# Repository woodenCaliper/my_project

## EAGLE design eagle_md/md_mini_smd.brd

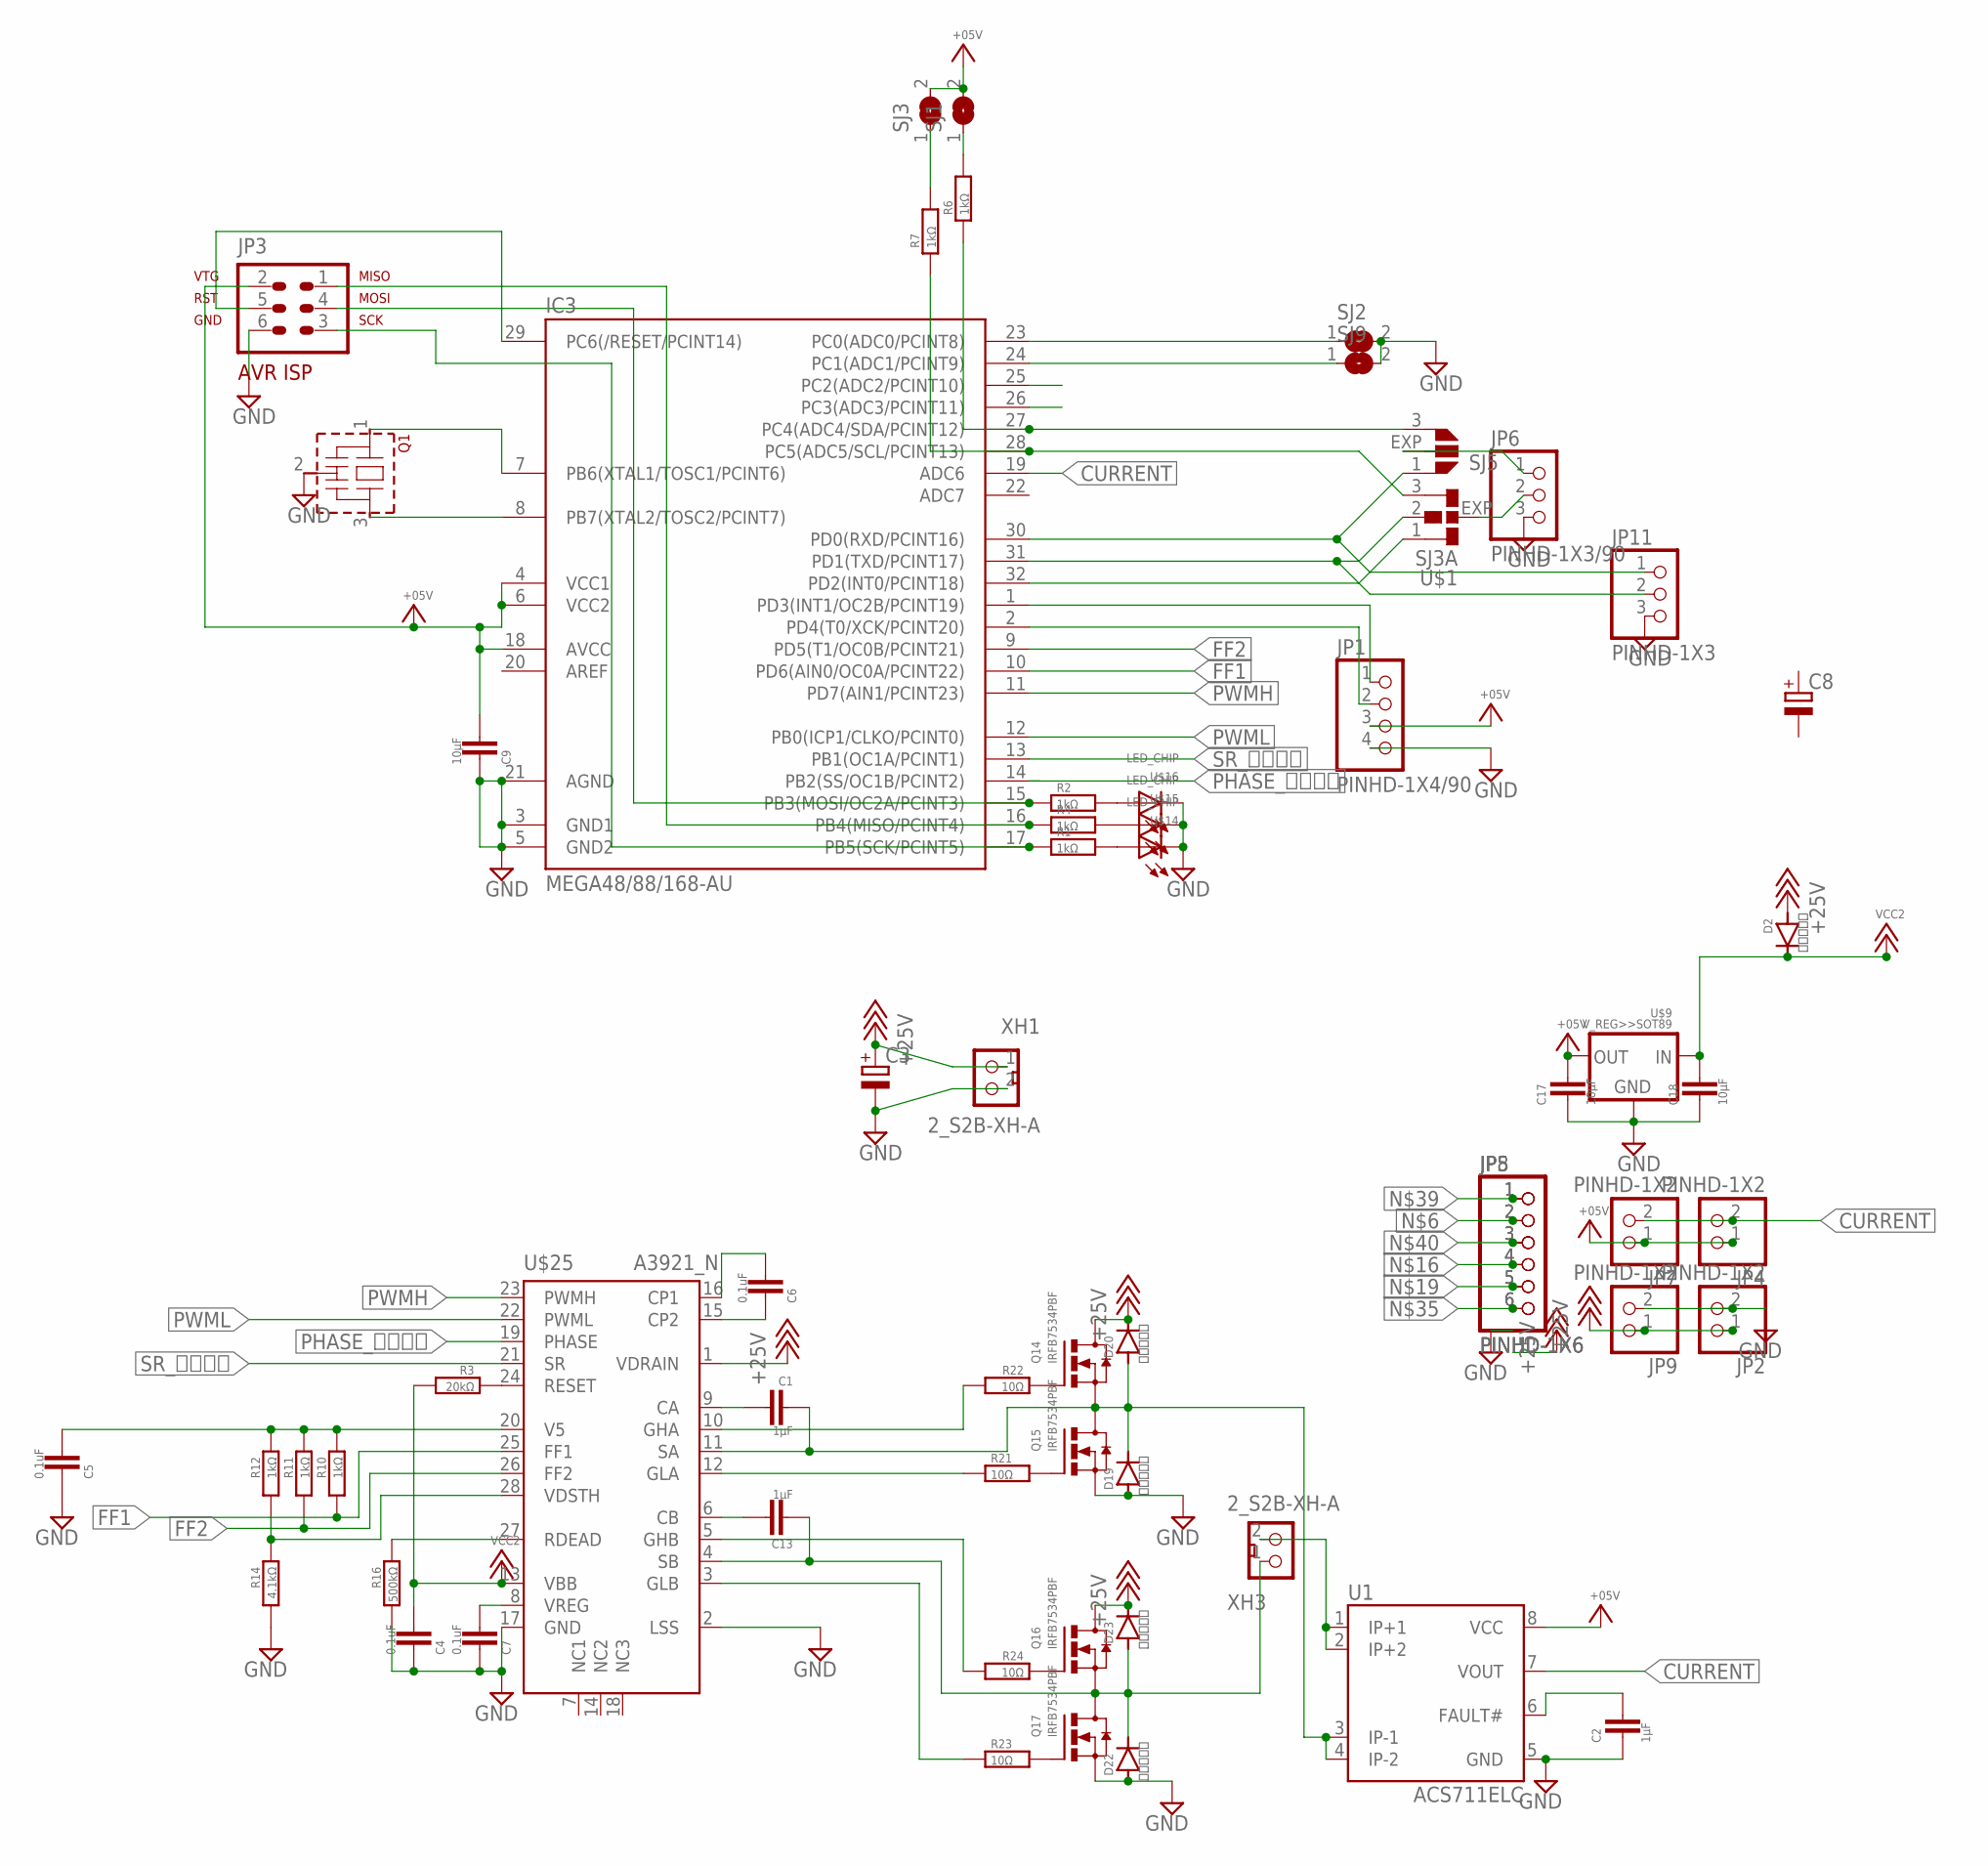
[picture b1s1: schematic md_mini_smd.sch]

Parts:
C1, C2, C13: 1μF; 2012
C3: CPOL-EUUD-6,3X8,8; UD-6,3X5,8_NICHICON
C4, C5, C6, C7: 0.1uF; 2012
C8: CPOL-EU150CLZ-1010; 150CLZ-1010
C9, C17, C18: 10μF; 2012
D2, D19, D20, D22, D23: ＭＳ１８Ｆ; MS18F
IC3: MEGA48/88/168-AU; TQFP32-08
JP1: PINHD-1X4/90; 1X04/90
JP2, JP4, JP7, JP9: PINHD-1X2; 1X02
JP3: AVR-ISP-6
JP5, JP8: PINHD-1X6; 1X06
JP6: PINHD-1X3/90; 1X03/90
JP11: PINHD-1X3; 1X03
Q1: CSTLS_G; CSTLS_G8
Q14, Q15, Q16, Q17: IRFB7534PBF; TO252
R1, R2, R4, R6, R7, R10, R11, R12: 1kΩ; 1608
R3: 20kΩ; 1608
R14: 4.1kΩ; 1608
R16: 500kΩ; 1608
R21, R22, R23, R24: 10Ω; 1608
SJ1, SJ2, SJ3, SJ9: SJSS; SJ_B
SJ5: SJ2; SJ2_A
U1: ACS711ELC; SOIC8
U$1: SJ3A; SJ3_A
U$9: V_REG>>SOT89; SOT89
U$14, U$15, U$16: LED_CHIP; 2012
U$25: A3921_N; TSSOP28_N
XH1, XH3: 2_S2B-XH-A; S2B-XH-A

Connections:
+5V: C9.1, C17.1, IC3.4 (VCC1), IC3.6 (VCC2), IC3.18 (AVCC), JP1.3, JP3.2, JP4.1, JP7.1, SJ1.2, SJ3.2, U1.8 (VCC), U$9.1 (OUT)
+18V: C3.+, D2.P$1 (A), D20.P$2 (C), D23.P$2 (C), JP2.1, JP9.1, Q14.3 (D), Q16.3 (D), U$25.1 (VDRAIN), XH1.1
CURRENT: IC3.19 (ADC6), JP4.2, JP7.2, U1.7 (VOUT)
FF1: IC3.10 (PD6(AIN0/OC0A/PCINT22)), R10.2, U$25.25 (FF1)
FF2: IC3.9 (PD5(T1/OC0B/PCINT21)), R11.2, U$25.26 (FF2)
GND: C2.2, C3.-, C4.2, C5.2, C7.2, C9.2, C17.2, C18.2, D19.P$1 (A), D22.P$1 (A), IC3.3 (GND1), IC3.5 (GND2), IC3.21 (AGND), JP1.4, JP2.2, JP3.6, JP6.3, JP9.2, JP11.3, Q1.2 (VSS), Q15.2 (S), Q17.2 (S), R14.2, R16.2, SJ2.2, SJ9.2, U1.5 (GND), U$9.2 (GND), U$9.2.1 (GND), U$14.P$2 (C), U$15.P$2 (C), U$16.P$2 (C), U$25.2 (LSS), U$25.17 (GND), XH1.2
unnamed: IC3.1 (PD3(INT1/OC2B/PCINT19)), JP1.1
unnamed: R6.2, SJ1.1
unnamed: U1.1 (IP+1), U1.2 (IP+2), XH3.2
unnamed: C6.1, U$25.16 (CP1)
unnamed: IC3.29 (PC6(/RESET/PCINT14)), JP3.5
unnamed: C13.2, D22.P$2 (C), D23.P$1 (A), JP5.2, JP8.2, Q16.2 (S), Q17.3 (D), U$25.4 (SB), XH3.1
unnamed: IC3.7 (PB6(XTAL1/TOSC1/PCINT6)), Q1.1
unnamed: IC3.8 (PB7(XTAL2/TOSC2/PCINT7)), Q1.3
unnamed: R1.2, U$14.P$1 (A)
unnamed: IC3.2 (PD4(T0/XCK/PCINT20)), JP1.2
unnamed: IC3.17 (PB5(SCK/PCINT5)), JP3.3, R1.1
unnamed: C1.1, U$25.9 (CA)
unnamed: R4.2, U$15.P$1 (A)
unnamed: JP5.4, JP8.4, R22.2, U$25.10 (GHA)
unnamed: R2.2, U$16.P$1 (A)
unnamed: JP6.2, U$1.EXP
unnamed: C1.2, D19.P$2 (C), D20.P$1 (A), JP5.5, JP8.5, Q14.2 (S), Q15.3 (D), U1.3 (IP-1), U1.4 (IP-2), U$25.11 (SA)
unnamed: R7.2, SJ3.1
unnamed: IC3.15 (PB3(MOSI/OC2A/PCINT3)), JP3.4, R2.1
unnamed: IC3.16 (PB4(MISO/PCINT4)), JP3.1, R4.1
unnamed: JP6.1, SJ5.EXP (2)
unnamed: IC3.32 (PD2(INT0/PCINT18)), U$1.1
unnamed: IC3.23 (PC0(ADC0/PCINT8)), SJ2.1
unnamed: IC3.24 (PC1(ADC1/PCINT9)), SJ9.1
unnamed: IC3.31 (PD1(TXD/PCINT17)), JP11.2, U$1.2
unnamed: IC3.30 (PD0(RXD/PCINT16)), JP11.1, SJ5.1
unnamed: C6.2, U$25.15 (CP2)
unnamed: IC3.28 (PC5(ADC5/SCL/PCINT13)), R7.1, U$1.3
unnamed: IC3.27 (PC4(ADC4/SDA/PCINT12)), R6.1, SJ5.3
unnamed: JP5.6, JP8.6, R21.1, U$25.12 (GLA)
unnamed: R3.1, U$25.24 (RESET)
unnamed: C7.1, U$25.8 (VREG)
unnamed: JP5.1, JP8.1, R24.2, U$25.5 (GHB)
unnamed: JP5.3, JP8.3, R23.1, U$25.3 (GLB)
unnamed: C13.1, U$25.6 (CB)
unnamed: R12.2, R14.1, U$25.28 (VDSTH)
unnamed: Q15.1 (G), R21.2
unnamed: R16.1, U$25.27 (RDEAD)
unnamed: C2.1, U1.6 (FAULT#)
unnamed: Q14.1 (G), R22.1
unnamed: Q17.1 (G), R23.2
unnamed: Q16.1 (G), R24.1
PHASE_正転逆転: IC3.14 (PB2(SS/OC1B/PCINT2)), U$25.19 (PHASE)
PWMH: IC3.11 (PD7(AIN1/PCINT23)), U$25.23 (PWMH)
PWML: IC3.12 (PB0(ICP1/CLKO/PCINT0)), U$25.22 (PWML)
SR_ブレーキ: IC3.13 (PB1(OC1A/PCINT1)), U$25.21 (SR)
V5: C5.1, R10.1, R11.1, R12.1, U$25.20 (V5)
VCC2: C4.1, C18.1, D2.P$2 (C), R3.2, U$9.3 (IN), U$25.13 (VBB)

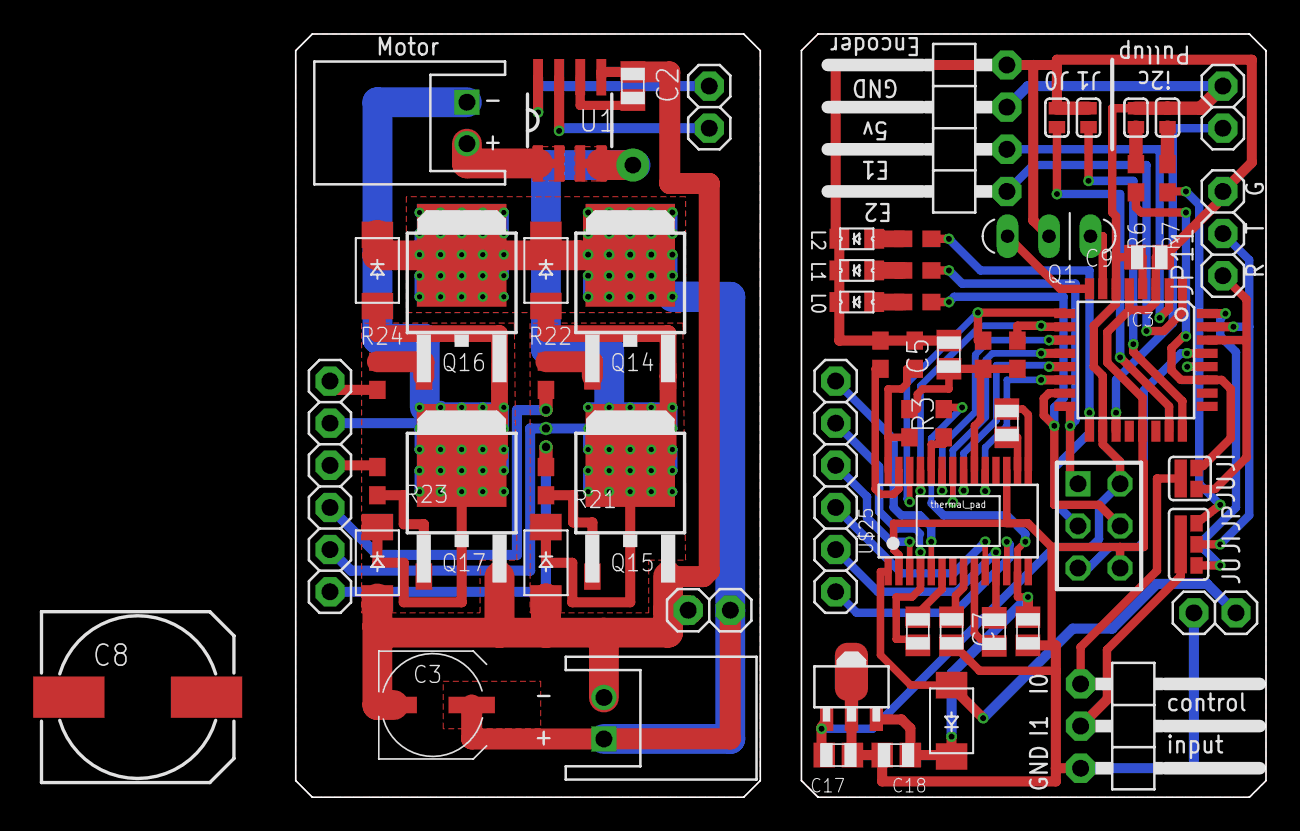
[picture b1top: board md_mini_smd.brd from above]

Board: 2 copper layers, 58.5 x 46.0 mm, 62 parts (0 on the bottom side), 54 nets.

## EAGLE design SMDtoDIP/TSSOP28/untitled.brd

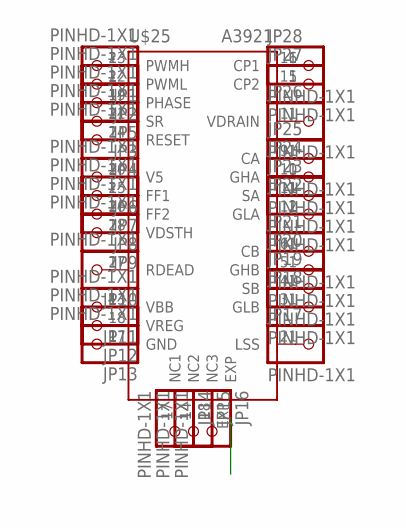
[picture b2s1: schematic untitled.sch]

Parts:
JP1, JP2, JP3, JP4, JP5, JP6, JP7, JP8, JP9, JP10, JP11, JP12, JP13, JP14, JP15, JP16, JP17, JP18, JP19, JP20, JP21, JP22, JP23, JP24, JP25, JP26, JP27, JP28: PINHD-1X1; 1X01
U$25: A3921; TSSOP28

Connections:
GND: JP13.1, U$25.17 (GND)
unnamed: JP2.1, U$25.22 (PWML)
unnamed: JP1.1, U$25.23 (PWMH)
unnamed: JP3.1, U$25.21 (SR)
unnamed: JP4.1, U$25.24 (RESET)
unnamed: JP5.1, U$25.19 (PHASE)
unnamed: JP6.1, U$25.20 (V5)
unnamed: JP7.1, U$25.25 (FF1)
unnamed: JP8.1, U$25.26 (FF2)
unnamed: JP9.1, U$25.28 (VDSTH)
unnamed: JP10.1, U$25.27 (RDEAD)
unnamed: JP12.1, U$25.8 (VREG)
unnamed: JP14.1, U$25.7 (NC1)
unnamed: JP15.1, U$25.14 (NC2)
unnamed: JP16.1, U$25.18 (NC3)
unnamed: JP17.1, U$25.2 (LSS)
unnamed: JP18.1, U$25.3 (GLB)
unnamed: JP21.1, U$25.6 (CB)
unnamed: JP22.1, U$25.12 (GLA)
unnamed: JP23.1, U$25.11 (SA)
unnamed: JP24.1, U$25.10 (GHA)
unnamed: JP25.1, U$25.9 (CA)
unnamed: JP27.1, U$25.15 (CP2)
unnamed: JP28.1, U$25.16 (CP1)
unnamed: JP20.1, U$25.5 (GHB)
unnamed: JP19.1, U$25.4 (SB)
VBB: JP11.1, U$25.13 (VBB)
VDRAIN: JP26.1, U$25.1 (VDRAIN)

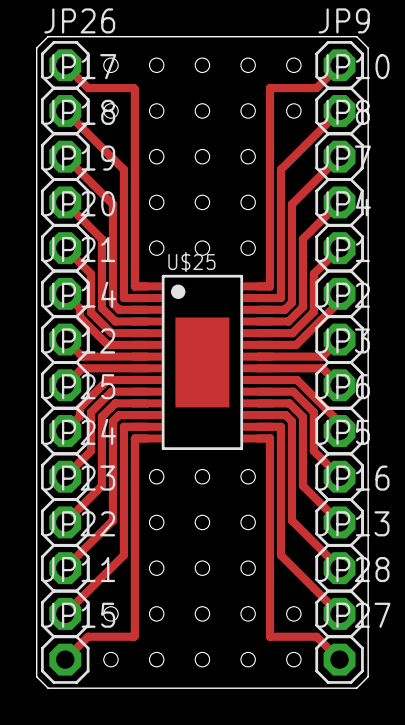
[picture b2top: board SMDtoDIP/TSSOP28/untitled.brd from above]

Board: 2 copper layers, 18.4 x 36.2 mm, 29 parts (0 on the bottom side), 28 nets.

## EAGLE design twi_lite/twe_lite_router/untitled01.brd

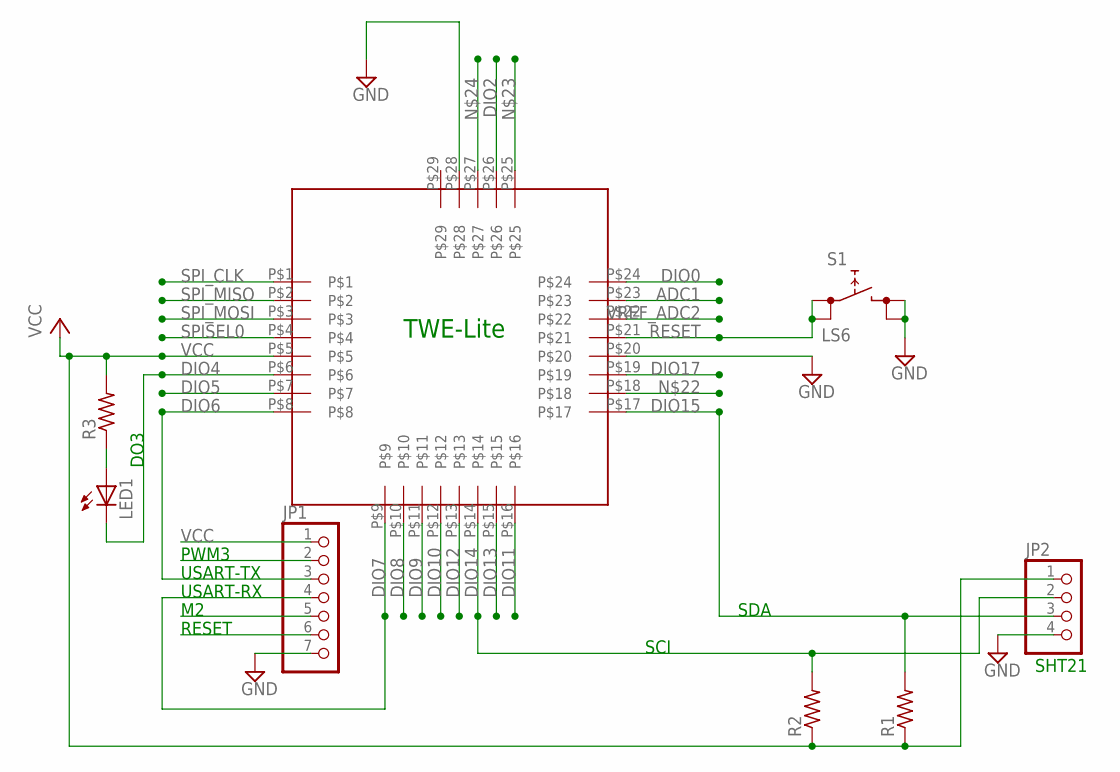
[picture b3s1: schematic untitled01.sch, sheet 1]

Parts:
JP1: PINHD-1X7; 1X07
JP2: PINHD-1X4/90; 1X04/90
LED1: LEDCHIP-LED0603; CHIP-LED0603
R1, R2, R3: R-US_R0805; R0805
S1: LS6
U$1: LITE

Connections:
ADC1: U$1.P$23
DIO0: U$1.P$24
DIO2: JP1.5, U$1.P$26
DIO4: LED1.C, U$1.P$6
DIO5: U$1.P$7
DIO6: JP1.3, U$1.P$8
DIO7: JP1.4, U$1.P$9
DIO8: U$1.P$10
DIO9: U$1.P$11
DIO10: U$1.P$12
DIO11: U$1.P$16
DIO12: U$1.P$13
DIO13: U$1.P$15
DIO14: JP2.2, R2.2, U$1.P$14
DIO15: JP2.3, R1.2, U$1.P$17
DIO17: U$1.P$19
GND: JP1.7, JP2.4, S1.P$3 (1), S1.P$4 (1), U$1.P$20, U$1.P$28; also elsewhere on the board
unnamed: LED1.A, R3.1
RESET: JP1.6, S1.P$1 (0), S1.P$2 (0), U$1.P$21
SPISEL0: U$1.P$4
SPI_CLK: U$1.P$1
SPI_MISO: JP1.2, U$1.P$2
SPI_MOSI: U$1.P$3
VCC: JP1.1, JP2.1, R1.1, R2.1, R3.2, U$1.P$5; also elsewhere on the board
VREF_ADC2: U$1.P$22

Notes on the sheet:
TWE-Lite
SCI
SDA
SHT21
USART-RX
USART-TX
RESET
DO3
PWM3

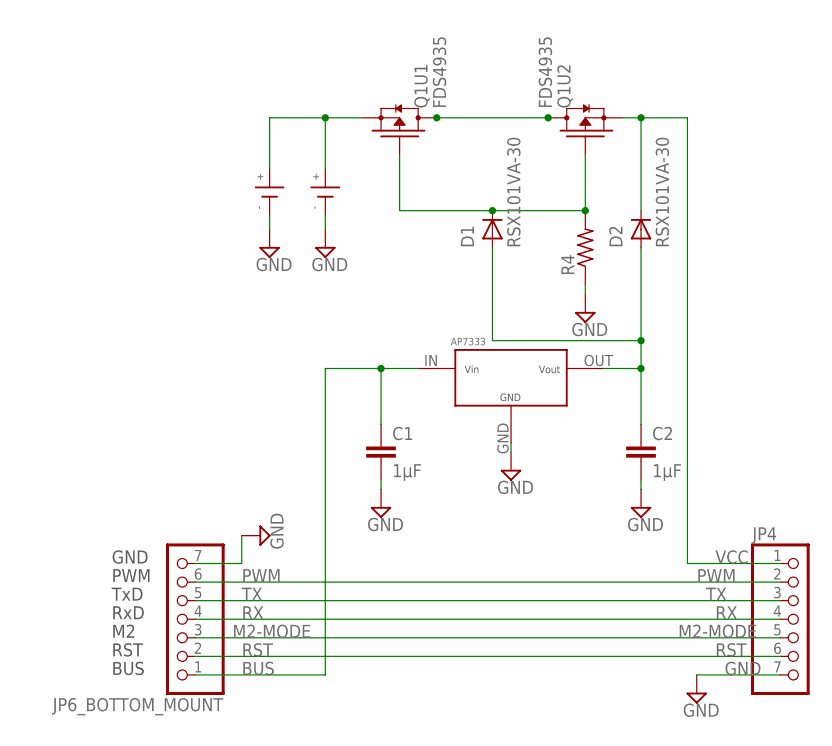
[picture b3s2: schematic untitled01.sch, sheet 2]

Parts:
C1, C2: 1μF; C1608
D1, D2: RSX101VA-30; RSX101VA
JP4, JP6_BOTTOM_MOUNT: PINHD-1X7; 1X07
Q1: FDS4935; SOIC(8PIN)
R4: R-US_M0805; M0805
U$2, U$3: CH004-2032LF
U$5: AP7333_SOT-23

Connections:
BAT: Q1.1 (S), U$2.+, U$3.+
BUS: C1.1, JP6_BOTTOM_MOUNT.1, U$5.IN
GND: C1.2, C2.2, JP4.7, JP6_BOTTOM_MOUNT.7, R4.1, U$2.-, U$3.-, U$5.GND; also elsewhere on the board
M2-MODE: JP4.5, JP6_BOTTOM_MOUNT.3
unnamed: D1.CATHODE (C), Q1.2 (G), Q1.4 (G), R4.2
unnamed: Q1.5 (D2), Q1.6 (D1), Q1.7 (D2), Q1.8 (D1)
PWM: JP4.2, JP6_BOTTOM_MOUNT.6
RST: JP4.6, JP6_BOTTOM_MOUNT.2; also elsewhere on the board
RX: JP4.4, JP6_BOTTOM_MOUNT.4
TX: JP4.3, JP6_BOTTOM_MOUNT.5
USB_BUS: C2.1, D1.ANODE (A), D2.ANODE (A), U$5.OUT
VCC: D2.CATHODE (C), JP4.1, Q1.3 (S); also elsewhere on the board

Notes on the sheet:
GND
PWM
TxD
RxD
RST
BUS

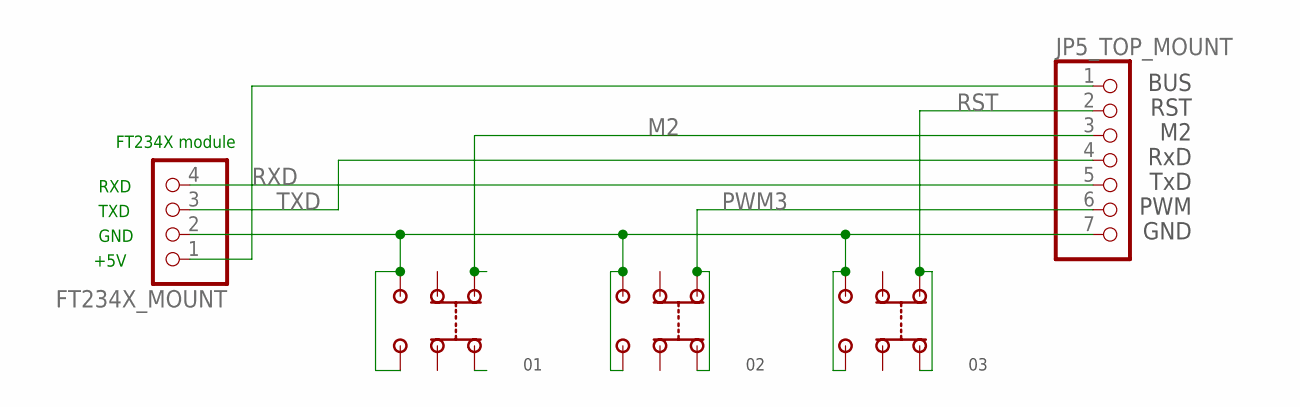
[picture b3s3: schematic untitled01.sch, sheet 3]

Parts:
01, 02, 03: SSSS213202
FT234X_MOUNT: PINHD-1X4; 1X04
JP5_TOP_MOUNT: PINHD-1X7; 1X07

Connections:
BUS_POWER: FT234X_MOUNT.1, JP5_TOP_MOUNT.1
GND: 01.3-1, 01.3-2, 02.3-1, 02.3-2, 03.3-1, 03.3-2, FT234X_MOUNT.2, JP5_TOP_MOUNT.7; also elsewhere on the board
M2: 01.1-2, JP5_TOP_MOUNT.3
PWM3: 02.1-1, 02.1-2, JP5_TOP_MOUNT.6
RST: 03.1-1, 03.1-2, JP5_TOP_MOUNT.2; also elsewhere on the board
RXD: FT234X_MOUNT.4, JP5_TOP_MOUNT.5
TXD: FT234X_MOUNT.3, JP5_TOP_MOUNT.4

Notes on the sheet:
+5V
GND
TXD
RXD
FT234X module
PWM
TxD
RxD
RST
BUS

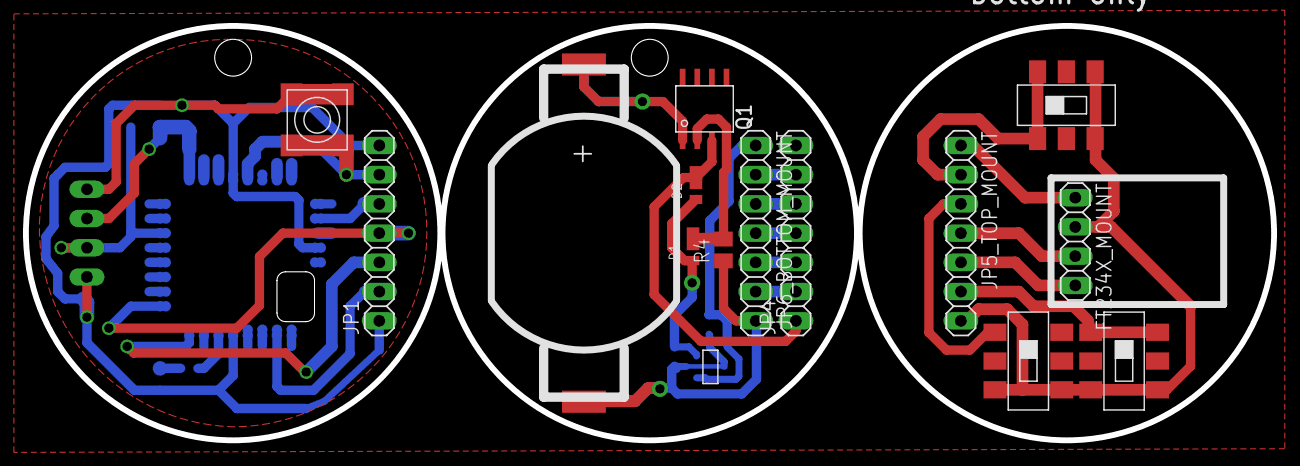
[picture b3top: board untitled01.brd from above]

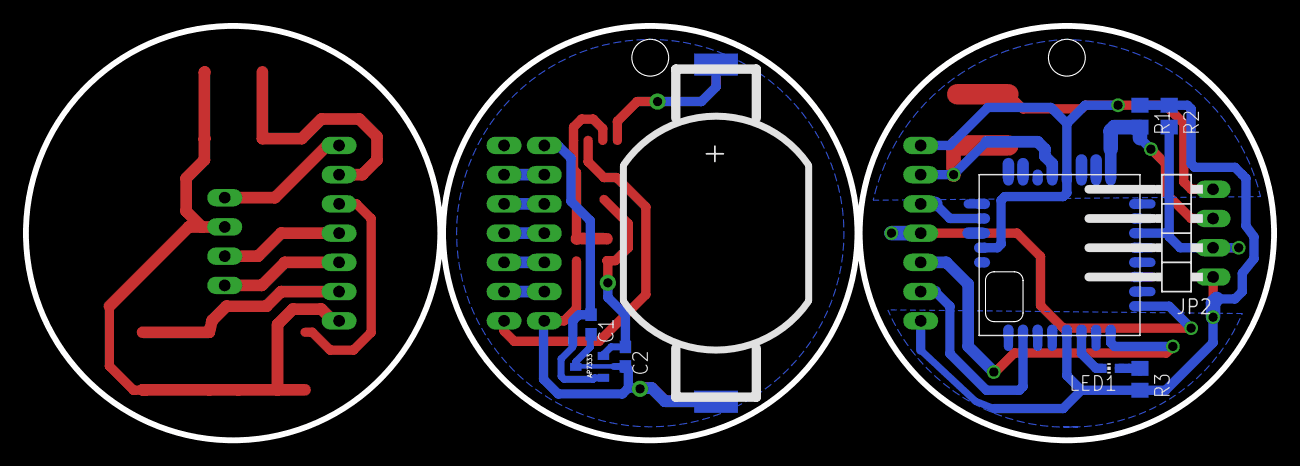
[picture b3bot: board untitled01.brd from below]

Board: 2 copper layers, 108.4 x 36.0 mm, 24 parts (10 on the bottom side), 26 nets.

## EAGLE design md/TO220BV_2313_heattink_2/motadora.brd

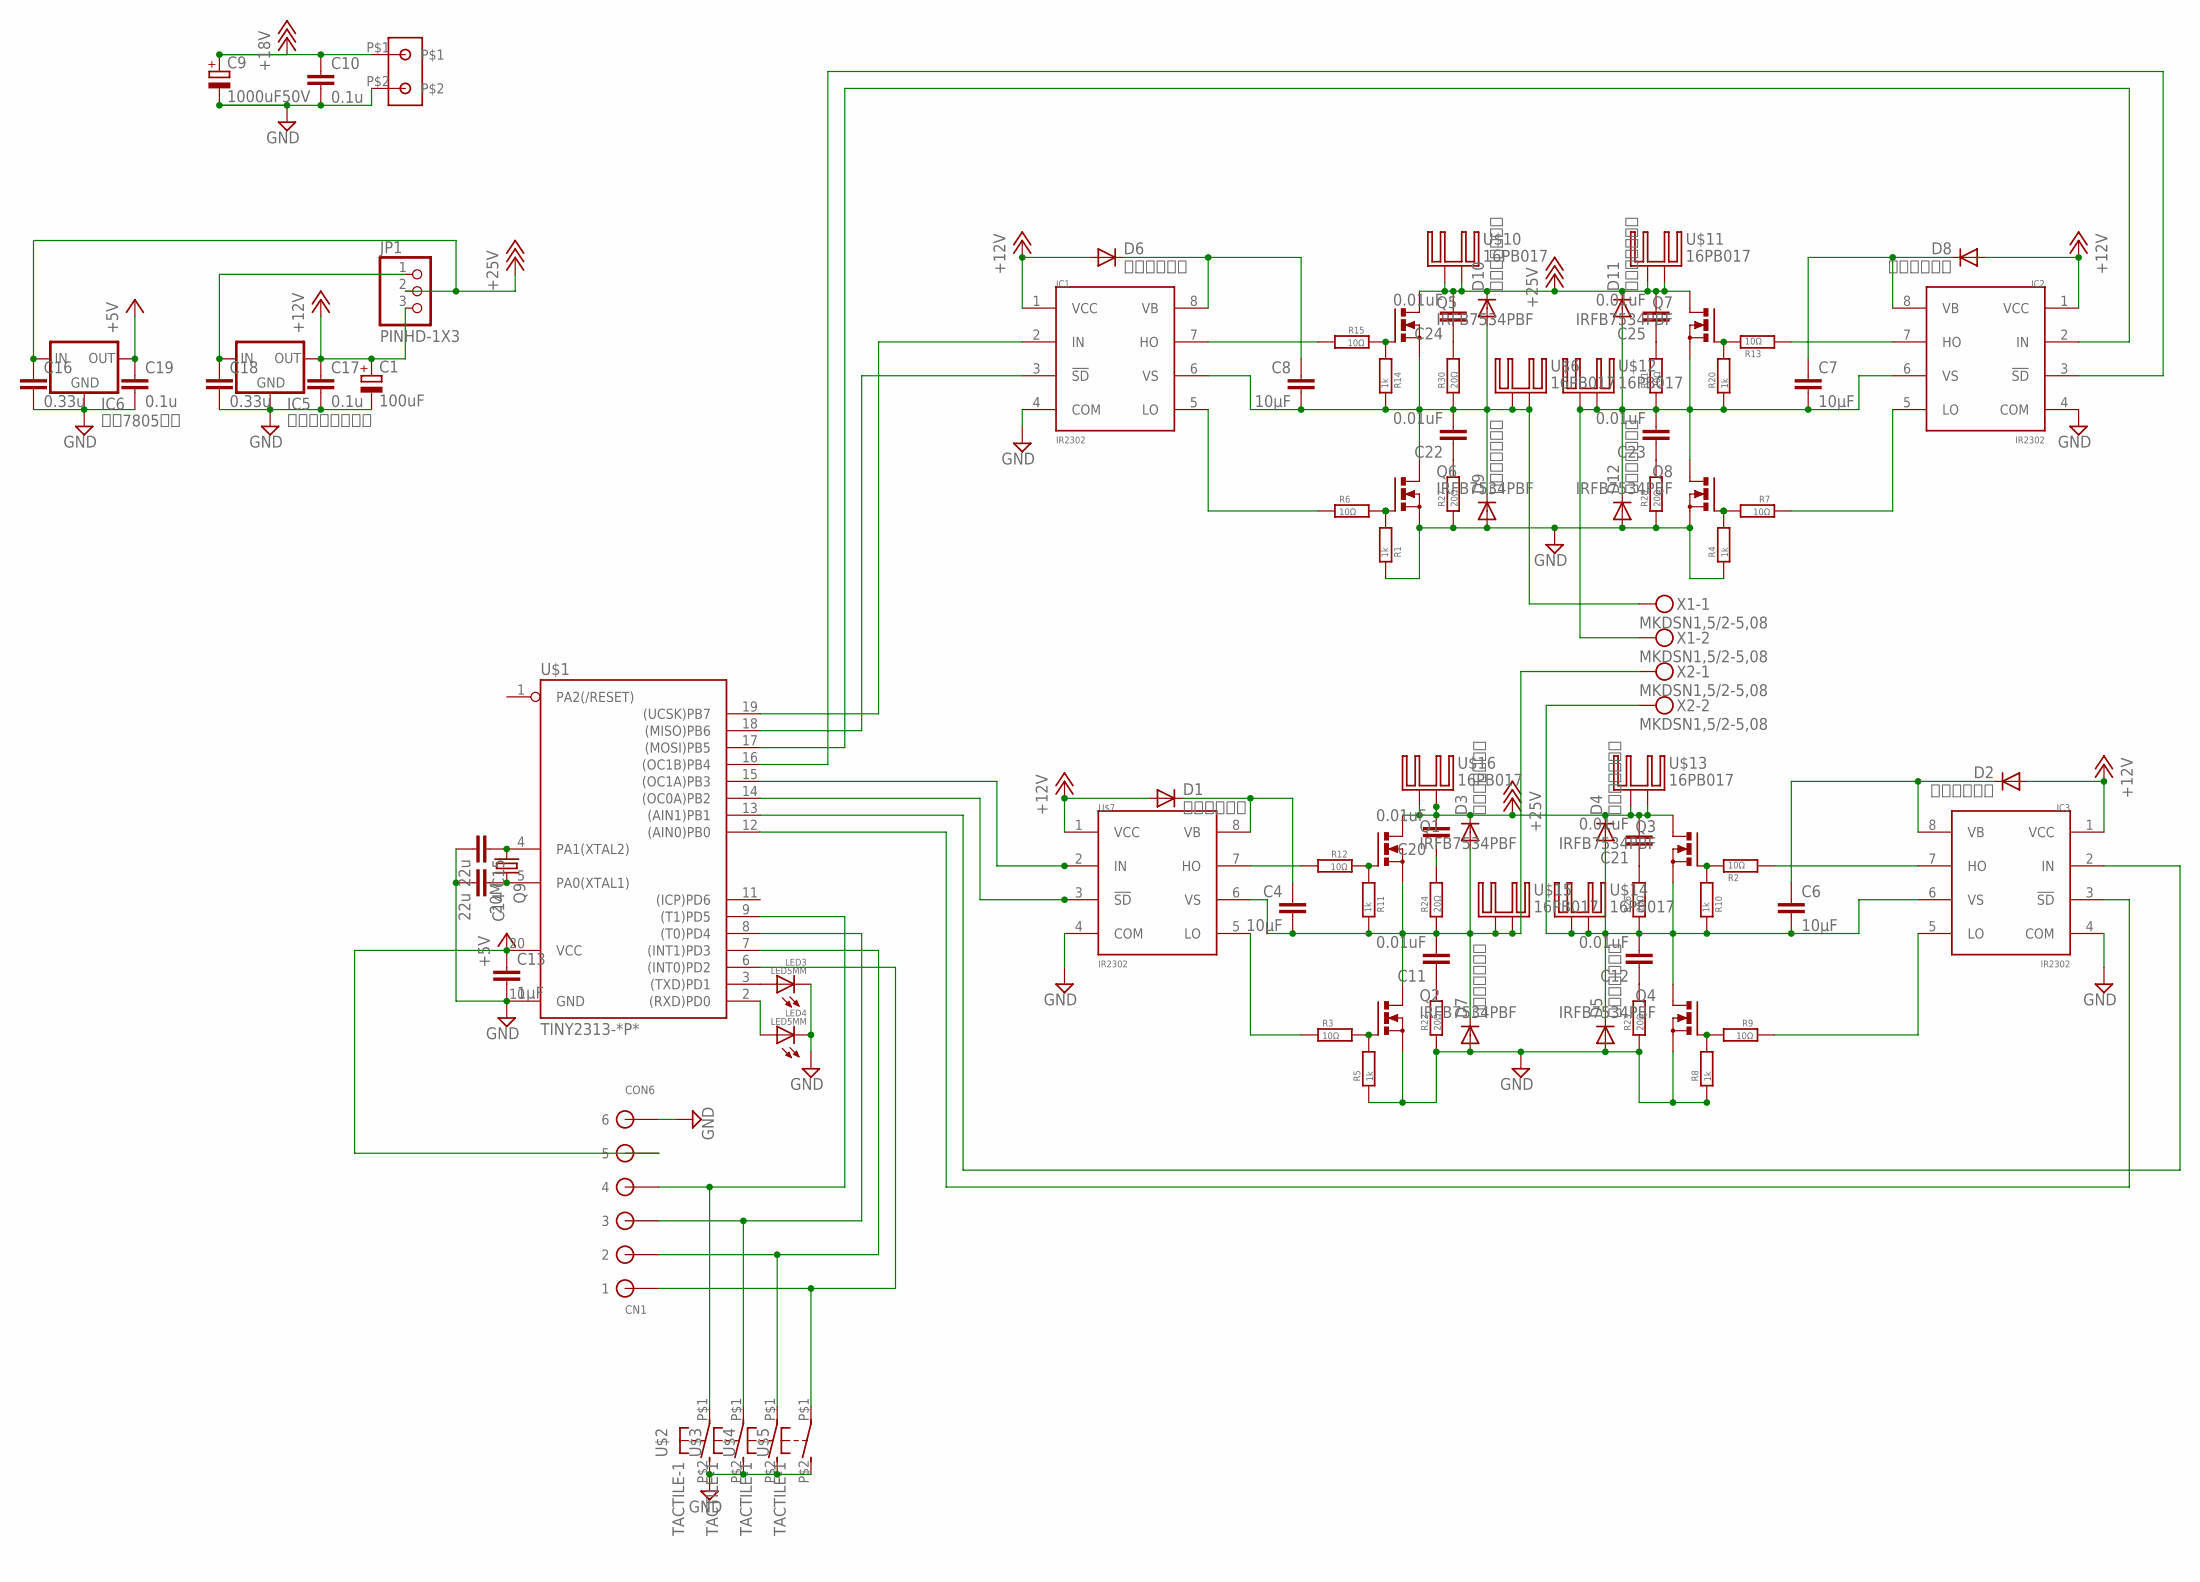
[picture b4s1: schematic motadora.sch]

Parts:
C1: 100uF; TT2D6
C4, C6, C7, C8: 10μF; C025-025X050
C9: 1000uF50V; E5-13
C10: 0.1u; C5B3
C11, C12, C20, C21, C22, C23, C24, C25: 0.01uF; C025-024X044
C13: 1μF; C050-025X075
C14, C15: 22u; C025-024X044
C16, C18: 0.33u; C025-025X050
C17, C19: 0.1u; C025-025X050
CN1: CON6
D1, D2, D6, D8: ＳＤ１０３Ａ; D-5
D3, D4, D5, D7, D9, D10, D11, D12: １１ＥＱＳ０６; D-5
IC1, IC2, IC3: IR2302; DIL08
IC5: ＬＭ７８１２ＣＶ; 78XXS
IC6: ＬＭ7805ＣＶ; 78XXS
JP1: PINHD-1X3; 1X03
LED3, LED4: LED5MM
Q1, Q2, Q3, Q4, Q5, Q6, Q7, Q8: IRFB7534PBF; TO220BV
Q9: 20M; HC49/S
R1, R4, R5, R8: 1k; 0207/7
R2, R12, R13, R15: 10Ω; 1/4W(2.5MM)_
R3, R6, R7, R9: 10Ω; 0207/10
R10, R11, R14, R20: 1k; 1/4W(2.5MM)_
R22, R23, R24, R26, R27, R28, R31: 20Ω; 0207/2V
R30: 20Ω; 1/4W(2.5MM)_
T2: TANSIDAI; A
U$1: TINY2313-*P*; DIL20
U$2, U$3, U$4, U$5: TACTILE-1; TACTILE
U$6, U$10, U$11, U$12, U$13, U$14, U$15, U$16: 16PB017
U$7: IR2302; DIL08
X1, X2: MKDSN1,5/2-5,08

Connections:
+5V: C13.1, C19.1, CN1.P$5 (5), IC6.OUT, U$1.20 (VCC)
+12V: C1.+, C17.1, D1.A, D2.A, D6.A, D8.A, IC1.1 (VCC), IC2.1 (VCC), IC3.1 (VCC), IC5.OUT, JP1.3, U$7.1 (VCC)
+18V: C9.+, C10.1, C16.1, C20.2, C21.2, C24.2, C25.2, D3.C, D4.C, D10.C, D11.C, IC6.IN, JP1.2, Q1.D, Q3.D, Q5.D, Q7.D, T2.P$1, U$10.P$1, U$10.P$2, U$11.P$1, U$11.P$2, U$13.P$1, U$13.P$2, U$16.P$1, U$16.P$2
GND: C1.-, C9.-, C10.2, C13.2, C14.2, C15.2, C16.2, C17.2, C18.2, C19.2, CN1.P$6 (6), D5.A, D7.A, D9.A, D12.A, IC1.4 (COM), IC2.4 (COM), IC3.4 (COM), IC5.GND, IC6.GND, LED3.K (C), LED4.K (C), Q2.S, Q4.S, Q6.S, Q8.S, R1.1, R4.1, R5.1, R8.1, R22.1, R23.1, R27.1, R28.1, T2.P$2, U$1.10 (GND), U$2.P$2 (S), U$3.P$2 (S), U$4.P$2 (S), U$5.P$2 (S), U$7.4 (COM)
unnamed: IC1.7 (HO), R15.4 (2)
unnamed: IC2.7 (HO), R13.4 (2)
unnamed: IC3.7 (HO), R2.4 (2)
unnamed: Q2.G, R3.2, R5.2
unnamed: R12.4 (2), U$7.7 (HO)
unnamed: IC1.5 (LO), R6.1
unnamed: Q1.G, R11.4 (2), R12.3 (1)
unnamed: C4.2, C11.2, D3.A, D7.C, Q1.S, Q2.D, R11.3 (1), R24.1, U$7.6 (VS), U$15.P$1, U$15.P$2, X2.1
unnamed: C4.1, D1.C, U$7.8 (VB)
unnamed: C6.1, D2.C, IC3.8 (VB)
unnamed: R3.1, U$7.5 (LO)
unnamed: C7.1, D8.C, IC2.8 (VB)
unnamed: Q5.G, R14.4 (2), R15.3 (1)
unnamed: C6.2, C12.2, D4.A, D5.C, IC3.6 (VS), Q3.S, Q4.D, R10.3 (1), R26.1, U$14.P$1, U$14.P$2, X2.2
unnamed: C8.1, D6.C, IC1.8 (VB)
unnamed: Q4.G, R8.2, R9.2
unnamed: CN1.P$2 (2), U$1.7 ((INT1)PD3), U$4.P$1
unnamed: C7.2, C23.2, D11.A, D12.C, IC2.6 (VS), Q7.S, Q8.D, R20.3 (1), R31.1, U$12.P$1, U$12.P$2, X1.2
unnamed: CN1.P$1 (1), U$1.6 ((INT0)PD2), U$5.P$1
unnamed: Q6.G, R1.2, R6.2
unnamed: C14.1, Q9.2, U$1.5 (PA0(XTAL1))
unnamed: LED3.A, U$1.3 ((TXD)PD1)
unnamed: IC1.3 (!SD), U$1.18 ((MISO)PB6)
unnamed: C15.1, Q9.1, U$1.4 (PA1(XTAL2))
unnamed: Q8.G, R4.2, R7.2
unnamed: C8.2, C22.2, D9.C, D10.A, IC1.6 (VS), Q5.S, Q6.D, R14.3 (1), R30.3 (1), U$6.P$1, U$6.P$2, X1.1
unnamed: LED4.A, U$1.2 ((RXD)PD0)
unnamed: C18.1, IC5.IN, JP1.1
unnamed: C11.1, R22.2
unnamed: C12.1, R23.2
unnamed: IC2.5 (LO), R7.1
unnamed: C20.1, R24.2
unnamed: C21.1, R26.2
unnamed: C22.1, R27.2
unnamed: C23.1, R28.2
unnamed: C24.1, R30.4 (2)
unnamed: C25.1, R31.2
unnamed: Q3.G, R2.3 (1), R10.4 (2)
unnamed: Q7.G, R13.3 (1), R20.4 (2)
unnamed: IC3.5 (LO), R9.1
unnamed: IC1.2 (IN), U$1.19 ((UCSK)PB7)
unnamed: IC2.2 (IN), U$1.17 ((MOSI)PB5)
unnamed: IC2.3 (!SD), U$1.16 ((OC1B)PB4)
unnamed: U$1.15 ((OC1A)PB3), U$7.2 (IN)
unnamed: U$1.14 ((OC0A)PB2), U$7.3 (!SD)
unnamed: IC3.2 (IN), U$1.13 ((AIN1)PB1)
unnamed: IC3.3 (!SD), U$1.12 ((AIN0)PB0)
unnamed: CN1.P$4 (4), U$1.9 ((T1)PD5), U$2.P$1
unnamed: CN1.P$3 (3), U$1.8 ((T0)PD4), U$3.P$1

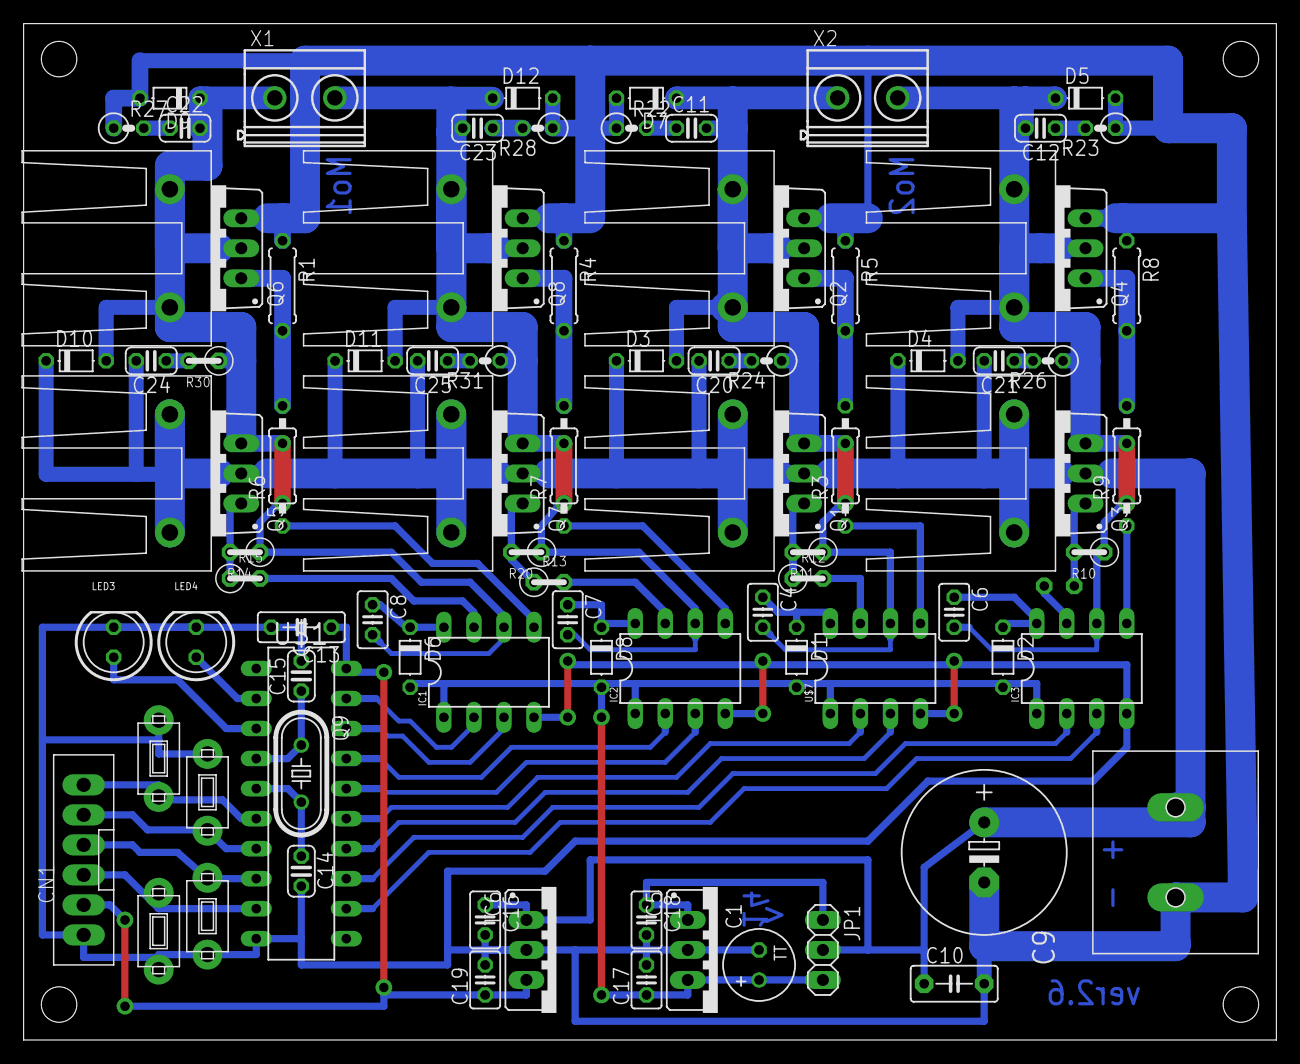
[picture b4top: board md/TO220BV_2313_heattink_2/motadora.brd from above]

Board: 2 copper layers, 106.0 x 86.0 mm, 93 parts (1 on the bottom side), 53 nets.
